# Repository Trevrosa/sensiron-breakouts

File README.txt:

solder on a sht4x OR sts4x (only one) and use with the mounting holes.

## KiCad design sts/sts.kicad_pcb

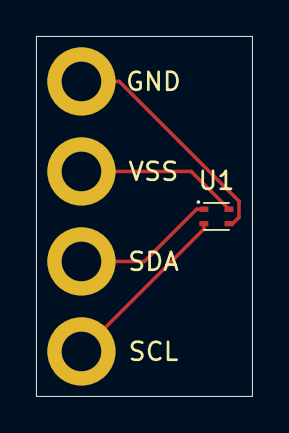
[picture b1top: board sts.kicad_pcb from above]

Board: 2 copper layers, 12.0 x 20.0 mm, 5 parts (0 on the bottom side), 4 nets.

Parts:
GND: MountingHole_Pad; MountingHole_2.2mm_M2_DIN965_Pad
SCL: MountingHole_Pad; MountingHole_2.2mm_M2_DIN965_Pad
SDA: MountingHole_Pad; MountingHole_2.2mm_M2_DIN965_Pad
U1: STS4X
VSS: MountingHole_Pad; MountingHole_2.2mm_M2_DIN965_Pad

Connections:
GND: GND.1, U1.3 (VDD)
unnamed: SCL.1, U1.2 (SCL)
unnamed: SDA.1, U1.1 (SDA)
VSS: U1.4 (VSS), VSS.1

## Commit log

2025-10-27 Add gerber.zip
2025-10-28 put the projects into one
2025-10-28 make the breakouts separate but in one pcb
2025-10-31 include drill files in gerber
2025-10-31 remove duplicate files in gerber
